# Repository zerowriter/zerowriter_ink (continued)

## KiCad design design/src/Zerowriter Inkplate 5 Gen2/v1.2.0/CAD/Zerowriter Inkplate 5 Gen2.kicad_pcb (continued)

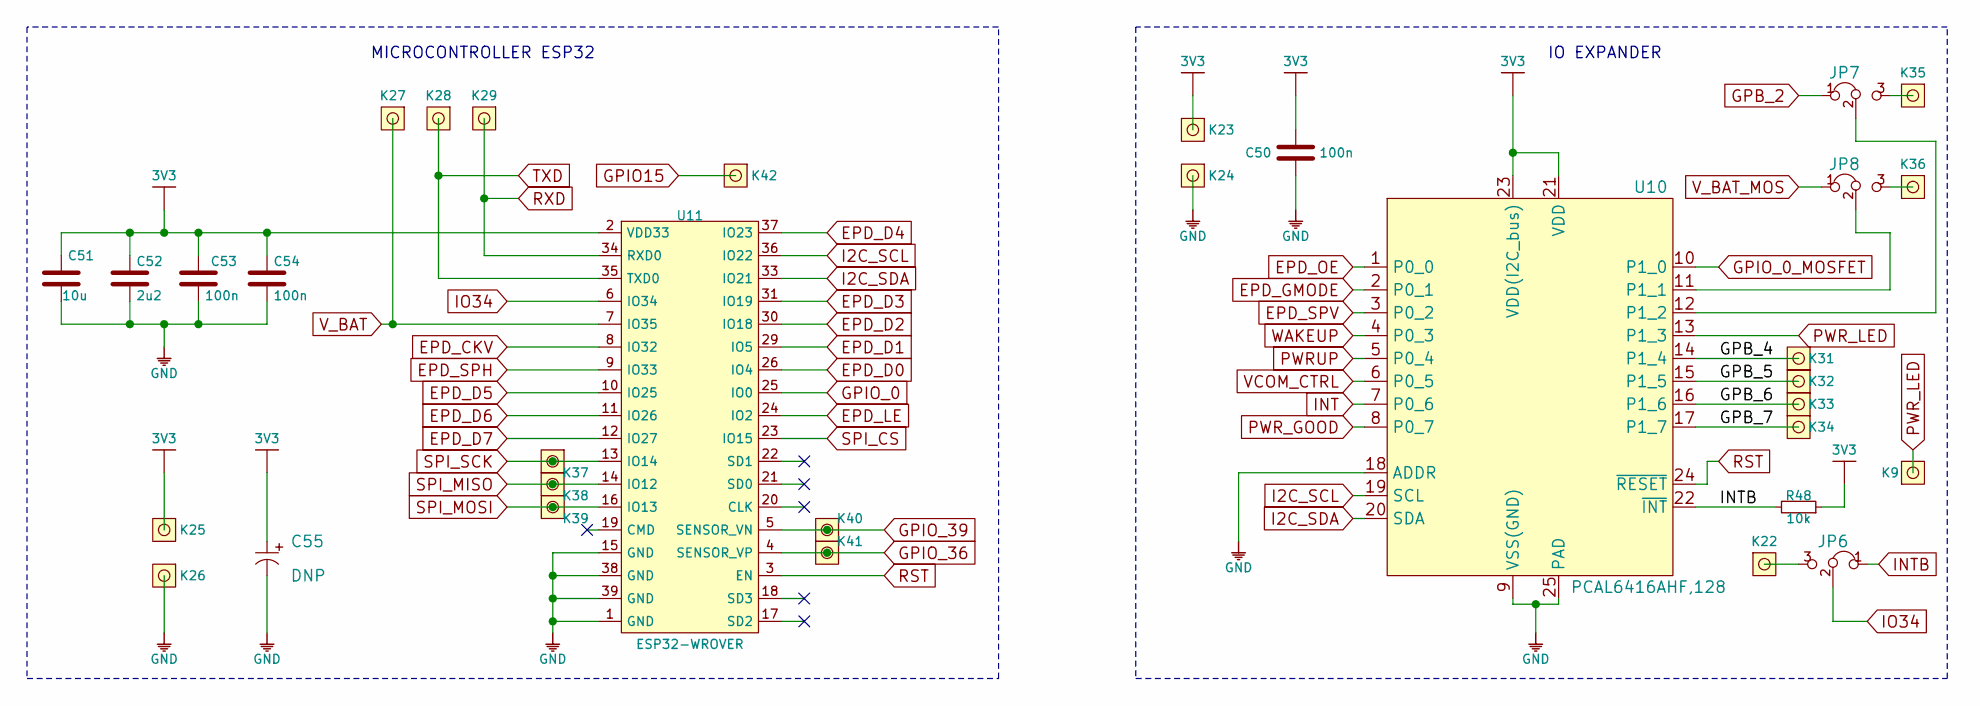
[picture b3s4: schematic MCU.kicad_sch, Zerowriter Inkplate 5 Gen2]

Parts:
C50, C53, C54: 100n; 0603C
C51: 10u; 1206C
C52: 2u2; 0603C
C55: DNP; 2917C
JP6, JP7, JP8: SMD_JUMPER_3_PAD_CONNECTED_LEFT_TRACE
K9, K22, K23, K24, K25, K26, K27, K28, K29, K31, K32, K33, K34, K35, K36, K37, K38, K39, K40, K41, K42: HEADER_MALE_1X1_Inkplate
R48: 10k; 0603R
U10: PCAL6416AHF,128
U11: ESP32-WROVER

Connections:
3V3: C50.2, C51.2, C52.2, C53.2, C54.2, C55.1 (+), K23.1, K25.1, R48.1, U10.21 (VDD), U10.23 (VDD(I2C_bus)), U11.2 (VDD33); also elsewhere on the board
/MCU/GPB_4: K31.1, U10.14 (P1_4)
/MCU/GPB_5: K32.1, U10.15 (P1_5)
/MCU/GPB_6: K33.1, U10.16 (P1_6)
/MCU/GPB_7: K34.1, U10.17 (P1_7)
EPD_CKV: U11.8 (IO32); also elsewhere on the board
EPD_D0: U11.26 (IO4); also elsewhere on the board
EPD_D1: U11.29 (IO5); also elsewhere on the board
EPD_D2: U11.30 (IO18); also elsewhere on the board
EPD_D3: U11.31 (IO19); also elsewhere on the board
EPD_D4: U11.37 (IO23); also elsewhere on the board
EPD_D5: U11.10 (IO25); also elsewhere on the board
EPD_D6: U11.11 (IO26); also elsewhere on the board
EPD_D7: U11.12 (IO27); also elsewhere on the board
EPD_GMODE: U10.2 (P0_1); also elsewhere on the board
EPD_LE: U11.24 (IO2); also elsewhere on the board
EPD_OE: U10.1 (P0_0); also elsewhere on the board
EPD_SPH: U11.9 (IO33); also elsewhere on the board
EPD_SPV: U10.3 (P0_2); also elsewhere on the board
GND: C50.1, C51.1, C52.1, C53.1, C54.1, C55.2 (-), K24.1, K26.1, U10.9 (VSS(GND)), U10.18 (ADDR), U10.25 (PAD), U11.1 (GND), U11.15 (GND), U11.38 (GND), U11.39 (GND); also elsewhere on the board
GPB_2: JP7.1; also elsewhere on the board
GPIO15: K42.1; also elsewhere on the board
GPIO_0: U11.25 (IO0); also elsewhere on the board
GPIO_0_MOSFET: U10.10 (P1_0); also elsewhere on the board
GPIO_36: K41.1, U11.4 (SENSOR_VP); also elsewhere on the board
GPIO_39: K40.1, U11.5 (SENSOR_VN); also elsewhere on the board
I2C_SCL: U10.19 (SCL), U11.36 (IO22); also elsewhere on the board
I2C_SDA: U10.20 (SDA), U11.33 (IO21); also elsewhere on the board
INT: U10.7 (P0_6); also elsewhere on the board
INTB: JP6.1, R48.2, U10.22 (~INT); also elsewhere on the board
IO34: JP6.2, U11.6 (IO34); also elsewhere on the board
unnamed: JP6.3, K22.1
unnamed: JP7.3, K35.1
unnamed: JP8.3, K36.1
unnamed: JP8.2, U10.11 (P1_1)
unnamed: JP7.2, U10.12 (P1_2)
PWRUP: U10.5 (P0_4); also elsewhere on the board
PWR_GOOD: U10.8 (P0_7); also elsewhere on the board
PWR_LED: K9.1, U10.13 (P1_3); also elsewhere on the board
RST: U10.24 (~RESET), U11.3 (EN); also elsewhere on the board
RXD: K29.1, U11.34 (RXD0); also elsewhere on the board
SPI_CS: U11.23 (IO15); also elsewhere on the board
SPI_MISO: K38.1, U11.14 (IO12); also elsewhere on the board
SPI_MOSI: K39.1, U11.16 (IO13); also elsewhere on the board
SPI_SCK: K37.1, U11.13 (IO14); also elsewhere on the board
TXD: K28.1, U11.35 (TXD0); also elsewhere on the board
VCOM_CTRL: U10.6 (P0_5); also elsewhere on the board
V_BAT: K27.1, U11.7 (IO35); also elsewhere on the board
V_BAT_MOS: JP8.1; also elsewhere on the board
WAKEUP: U10.4 (P0_3); also elsewhere on the board

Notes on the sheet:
IO EXPANDER
MICROCONTROLLER ESP32

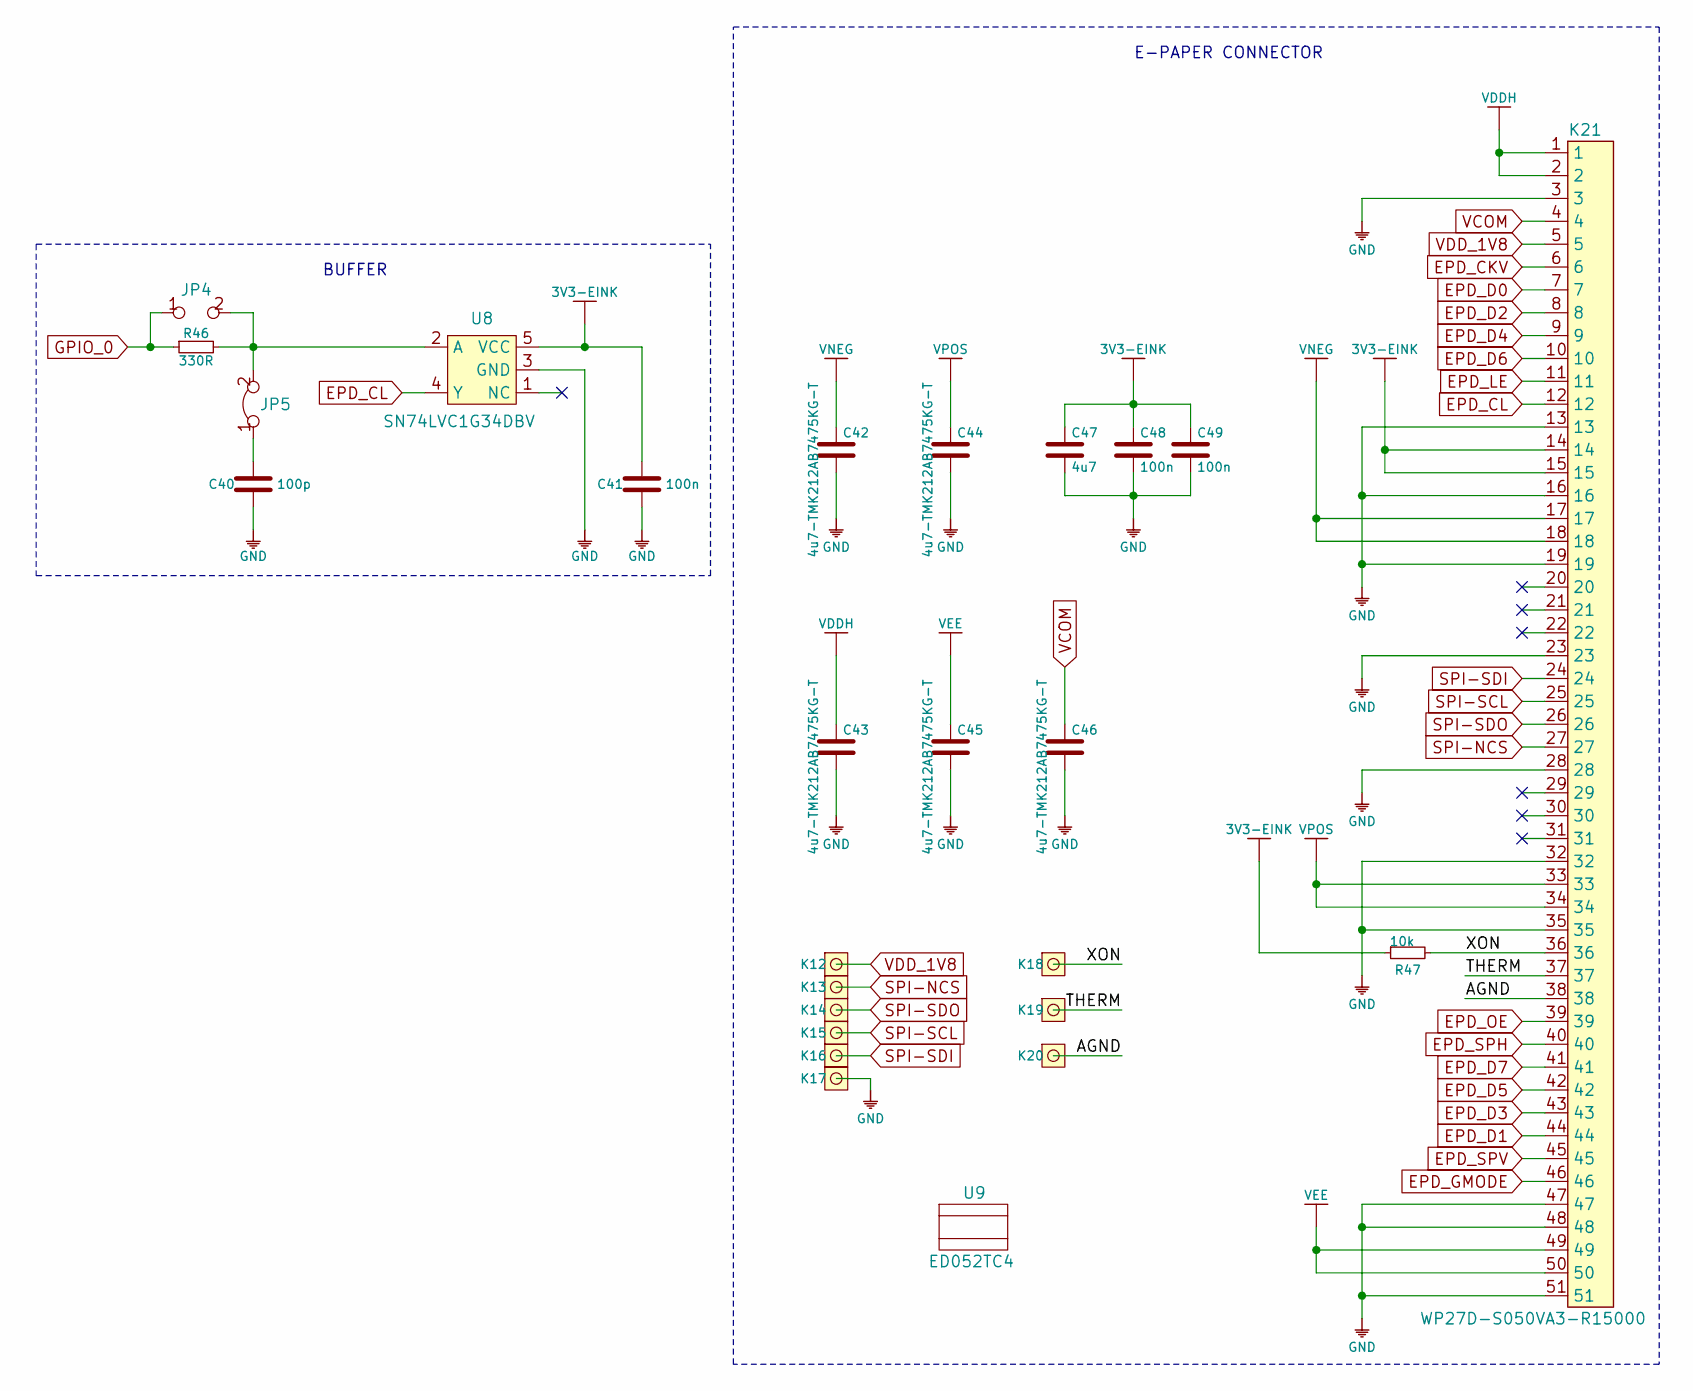
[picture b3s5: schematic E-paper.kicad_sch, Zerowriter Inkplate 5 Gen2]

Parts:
C40: 100p; 0603C
C41, C48, C49: 100n; 0603C
C42, C43, C44, C45, C46: 4u7-TMK212AB7475KG-T; 0805C
C47: 4u7; 0603C
JP4: SMD_JUMPER
JP5: SMD-JUMPER-CONNECTED_TRACE_SOLDERMASK
K12, K13, K14, K15, K16, K17, K18, K19, K20: HEADER_MALE_1X1_Inkplate
K21: WP27D-S050VA3-R15000
R46: 330R; 0603R
R47: 10k; 0603R
U8: SN74LVC1G34DBV
U9: ED052TC4

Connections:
3V3-EINK: C41.2, C47.2, C48.2, C49.2, K21.14, K21.15, R47.1, U8.5 (VCC); also elsewhere on the board
/E-paper/AGND: K20.1, K21.38
/E-paper/THERM: K19.1, K21.37
/E-paper/XON: K18.1, K21.36, R47.2
EPD_CKV: K21.6; also elsewhere on the board
EPD_CL: K21.12, U8.4 (Y)
EPD_D0: K21.7; also elsewhere on the board
EPD_D1: K21.44; also elsewhere on the board
EPD_D2: K21.8; also elsewhere on the board
EPD_D3: K21.43; also elsewhere on the board
EPD_D4: K21.9; also elsewhere on the board
EPD_D5: K21.42; also elsewhere on the board
EPD_D6: K21.10; also elsewhere on the board
EPD_D7: K21.41; also elsewhere on the board
EPD_GMODE: K21.46; also elsewhere on the board
EPD_LE: K21.11; also elsewhere on the board
EPD_OE: K21.39; also elsewhere on the board
EPD_SPH: K21.40; also elsewhere on the board
EPD_SPV: K21.45; also elsewhere on the board
GND: C40.1, C41.1, C42.1, C43.1, C44.1, C45.1, C46.1, C47.1, C48.1, C49.1, K17.1, K21.3, K21.13, K21.16, K21.19, K21.23, K21.28, K21.32, K21.35, K21.47, K21.48, K21.51, U8.3 (GND); also elsewhere on the board
GPIO_0: JP4.1, R46.1; also elsewhere on the board
unnamed: C40.2, JP5.1
unnamed: JP4.2, JP5.2, R46.2, U8.2 (A)
SPI-NCS: K13.1, K21.27
SPI-SCL: K15.1, K21.25
SPI-SDI: K16.1, K21.24
SPI-SDO: K14.1, K21.26
VCOM: C46.2, K21.4; also elsewhere on the board
VDDH: C43.2, K21.1, K21.2; also elsewhere on the board
VDD_1V8: K12.1, K21.5
VEE: C45.2, K21.49, K21.50; also elsewhere on the board
VNEG: C42.2, K21.17, K21.18; also elsewhere on the board
VPOS: C44.2, K21.33, K21.34; also elsewhere on the board

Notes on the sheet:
E-PAPER CONNECTOR
BUFFER

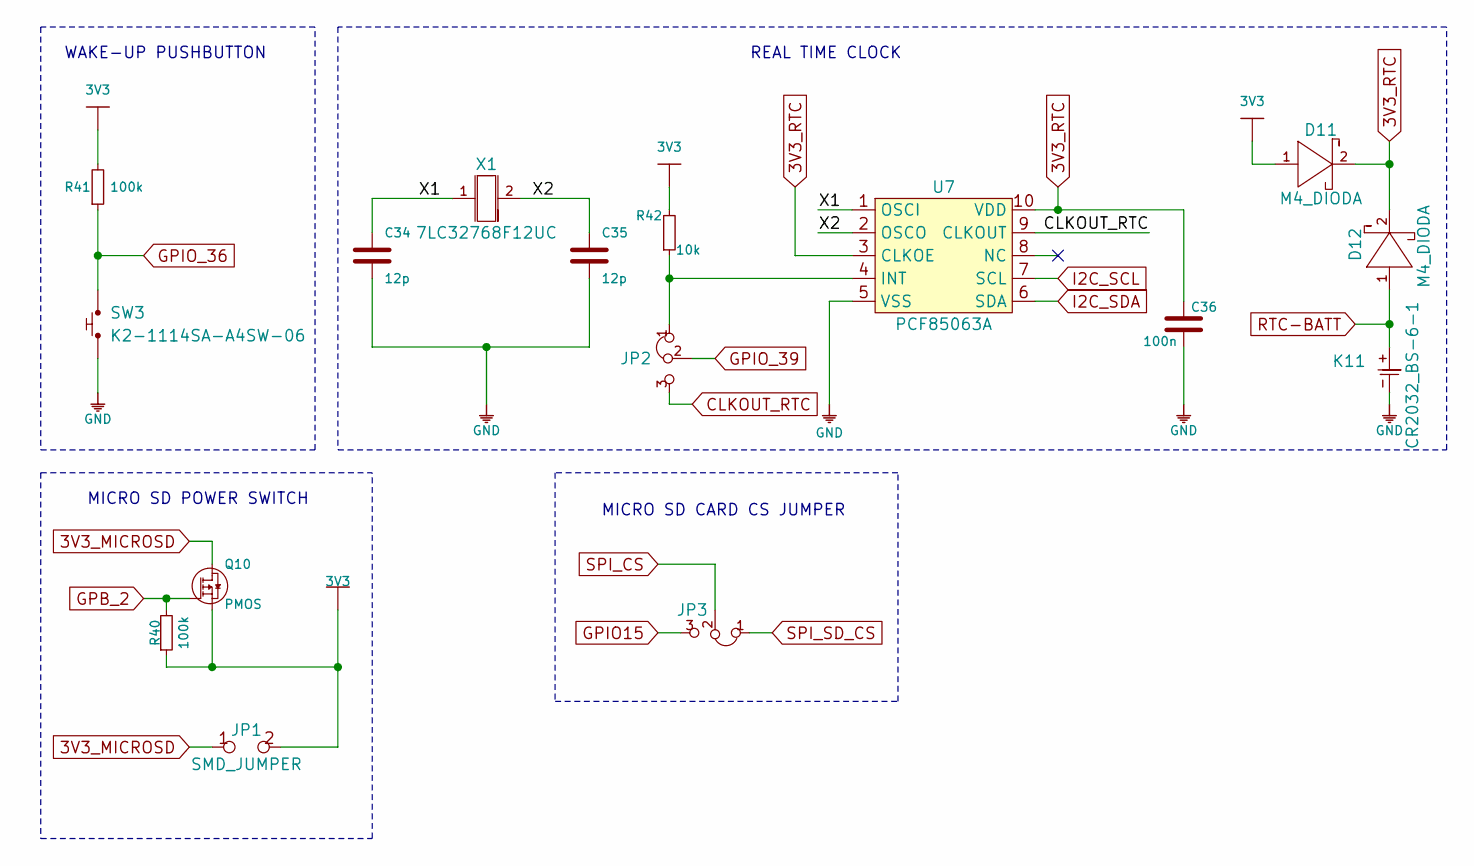
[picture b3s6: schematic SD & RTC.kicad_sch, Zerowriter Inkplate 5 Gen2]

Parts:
C34, C35: 12p; 0603C
C36: 100n; 0603C
D11, D12: M4_DIODA
JP1: SMD_JUMPER
JP2, JP3: SMD_JUMPER_3_PAD_CONNECTED_LEFT_TRACE
K11: CR2032_BS-6-1; CR2032-BS-6-1
Q10: PMOS; SOT-23-3
R40, R41: 100k; 0603R
R42: 10k; 0603R
SW3: K2-1114SA-A4SW-06
U7: PCF85063A
X1: 7LC32768F12UC; ABS07AIG-32.768KHZ-7-D-T

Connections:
3V3: D11.1 (A), JP1.2, Q10.2 (S), R40.1, R41.2, R42.2; also elsewhere on the board
3V3_MICROSD: JP1.1, Q10.3 (D); also elsewhere on the board
3V3_RTC: C36.2, D11.2 (K), D12.2 (K), U7.3 (CLKOE), U7.10 (VDD); also elsewhere on the board
/SD & RTC/X1: C34.2, U7.1 (OSCI), X1.1
/SD & RTC/X2: C35.2, U7.2 (OSCO), X1.2
CLKOUT_RTC: JP2.3, U7.9 (CLKOUT); also elsewhere on the board
GND: C34.1, C35.1, C36.1, K11.-, SW3.1, U7.5 (VSS); also elsewhere on the board
GPB_2: Q10.1 (G), R40.2; also elsewhere on the board
GPIO15: JP3.3; also elsewhere on the board
GPIO_36: R41.1, SW3.2; also elsewhere on the board
GPIO_39: JP2.2; also elsewhere on the board
I2C_SCL: U7.7 (SCL); also elsewhere on the board
I2C_SDA: U7.6 (SDA); also elsewhere on the board
unnamed: JP2.1, R42.1, U7.4 (INT)
RTC-BATT: D12.1 (A), K11.+; also elsewhere on the board
SPI_CS: JP3.2; also elsewhere on the board
SPI_SD_CS: JP3.1; also elsewhere on the board

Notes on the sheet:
REAL TIME CLOCK
MICRO SD CARD CS JUMPER
WAKE-UP PUSHBUTTON
MICRO SD POWER SWITCH

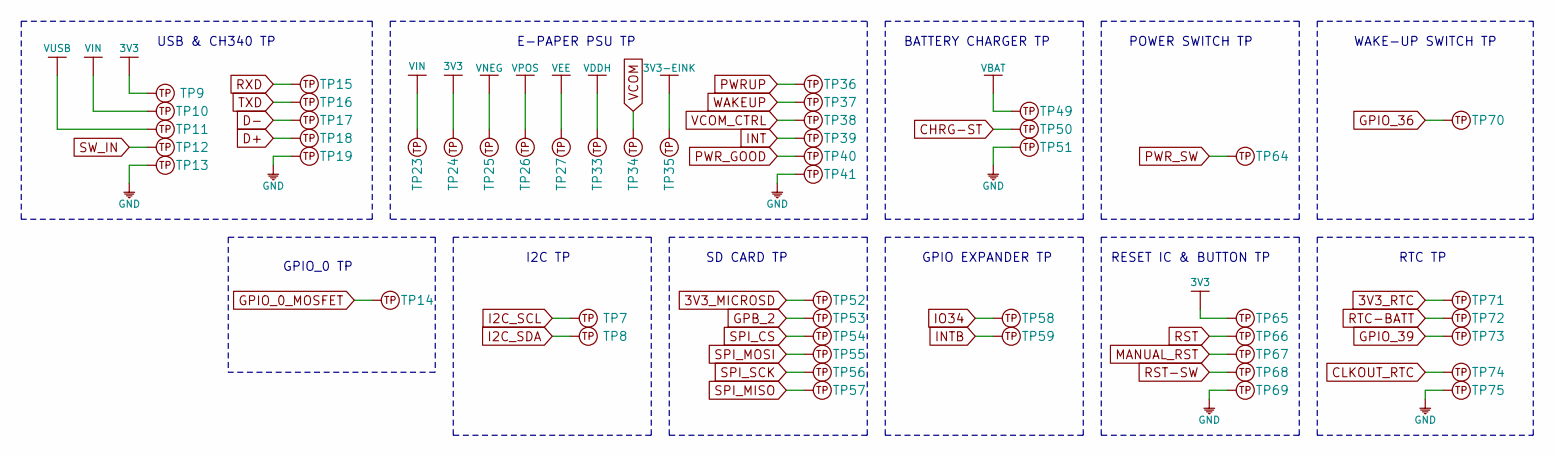
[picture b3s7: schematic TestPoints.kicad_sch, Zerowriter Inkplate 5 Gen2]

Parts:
TP7, TP8, TP9, TP10, TP11, TP12, TP13, TP14, TP15, TP16, TP17, TP18, TP19, TP23, TP24, TP25, TP26, TP27, TP33, TP34, TP35, TP36, TP37, TP38, TP39, TP40, TP41, TP49, TP50, TP51, TP52, TP53, TP54, TP55, TP56, TP57, TP58, TP59, TP64, TP65, TP66, TP67, TP68, TP69, TP70, TP71, TP72, TP73, TP74, TP75: Test_Point_SMD_0.8mm

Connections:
3V3: TP9.TP, TP24.TP, TP65.TP; also elsewhere on the board
3V3-EINK: TP35.TP; also elsewhere on the board
3V3_MICROSD: TP52.TP; also elsewhere on the board
3V3_RTC: TP71.TP; also elsewhere on the board
CHRG-ST: TP50.TP; also elsewhere on the board
CLKOUT_RTC: TP74.TP; also elsewhere on the board
D+: TP18.TP; also elsewhere on the board
D-: TP17.TP; also elsewhere on the board
GND: TP13.TP, TP19.TP, TP41.TP, TP51.TP, TP69.TP, TP75.TP; also elsewhere on the board
GPB_2: TP53.TP; also elsewhere on the board
GPIO_0_MOSFET: TP14.TP; also elsewhere on the board
GPIO_36: TP70.TP; also elsewhere on the board
GPIO_39: TP73.TP; also elsewhere on the board
I2C_SCL: TP7.TP; also elsewhere on the board
I2C_SDA: TP8.TP; also elsewhere on the board
INT: TP39.TP; also elsewhere on the board
INTB: TP59.TP; also elsewhere on the board
IO34: TP58.TP; also elsewhere on the board
MANUAL_RST: TP67.TP; also elsewhere on the board
PWRUP: TP36.TP; also elsewhere on the board
PWR_GOOD: TP40.TP; also elsewhere on the board
PWR_SW: TP64.TP; also elsewhere on the board
RST: TP66.TP; also elsewhere on the board
RST-SW: TP68.TP; also elsewhere on the board
RTC-BATT: TP72.TP; also elsewhere on the board
RXD: TP15.TP; also elsewhere on the board
SPI_CS: TP54.TP; also elsewhere on the board
SPI_MISO: TP57.TP; also elsewhere on the board
SPI_MOSI: TP55.TP; also elsewhere on the board
SPI_SCK: TP56.TP; also elsewhere on the board
SW_IN: TP12.TP; also elsewhere on the board
TXD: TP16.TP; also elsewhere on the board
VBAT: TP49.TP; also elsewhere on the board
VCOM: TP34.TP; also elsewhere on the board
VCOM_CTRL: TP38.TP; also elsewhere on the board
VDDH: TP33.TP; also elsewhere on the board
VEE: TP27.TP; also elsewhere on the board
VIN: TP10.TP, TP23.TP; also elsewhere on the board
VNEG: TP25.TP; also elsewhere on the board
VPOS: TP26.TP; also elsewhere on the board
VUSB: TP11.TP; also elsewhere on the board
WAKEUP: TP37.TP; also elsewhere on the board

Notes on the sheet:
GPIO EXPANDER TP
POWER SWITCH TP
RESET IC & BUTTON TP
BATTERY CHARGER TP
GPIO_0 TP
SD CARD TP
I2C TP
USB & CH340 TP
WAKE-UP SWITCH TP
RTC TP
E-PAPER PSU TP

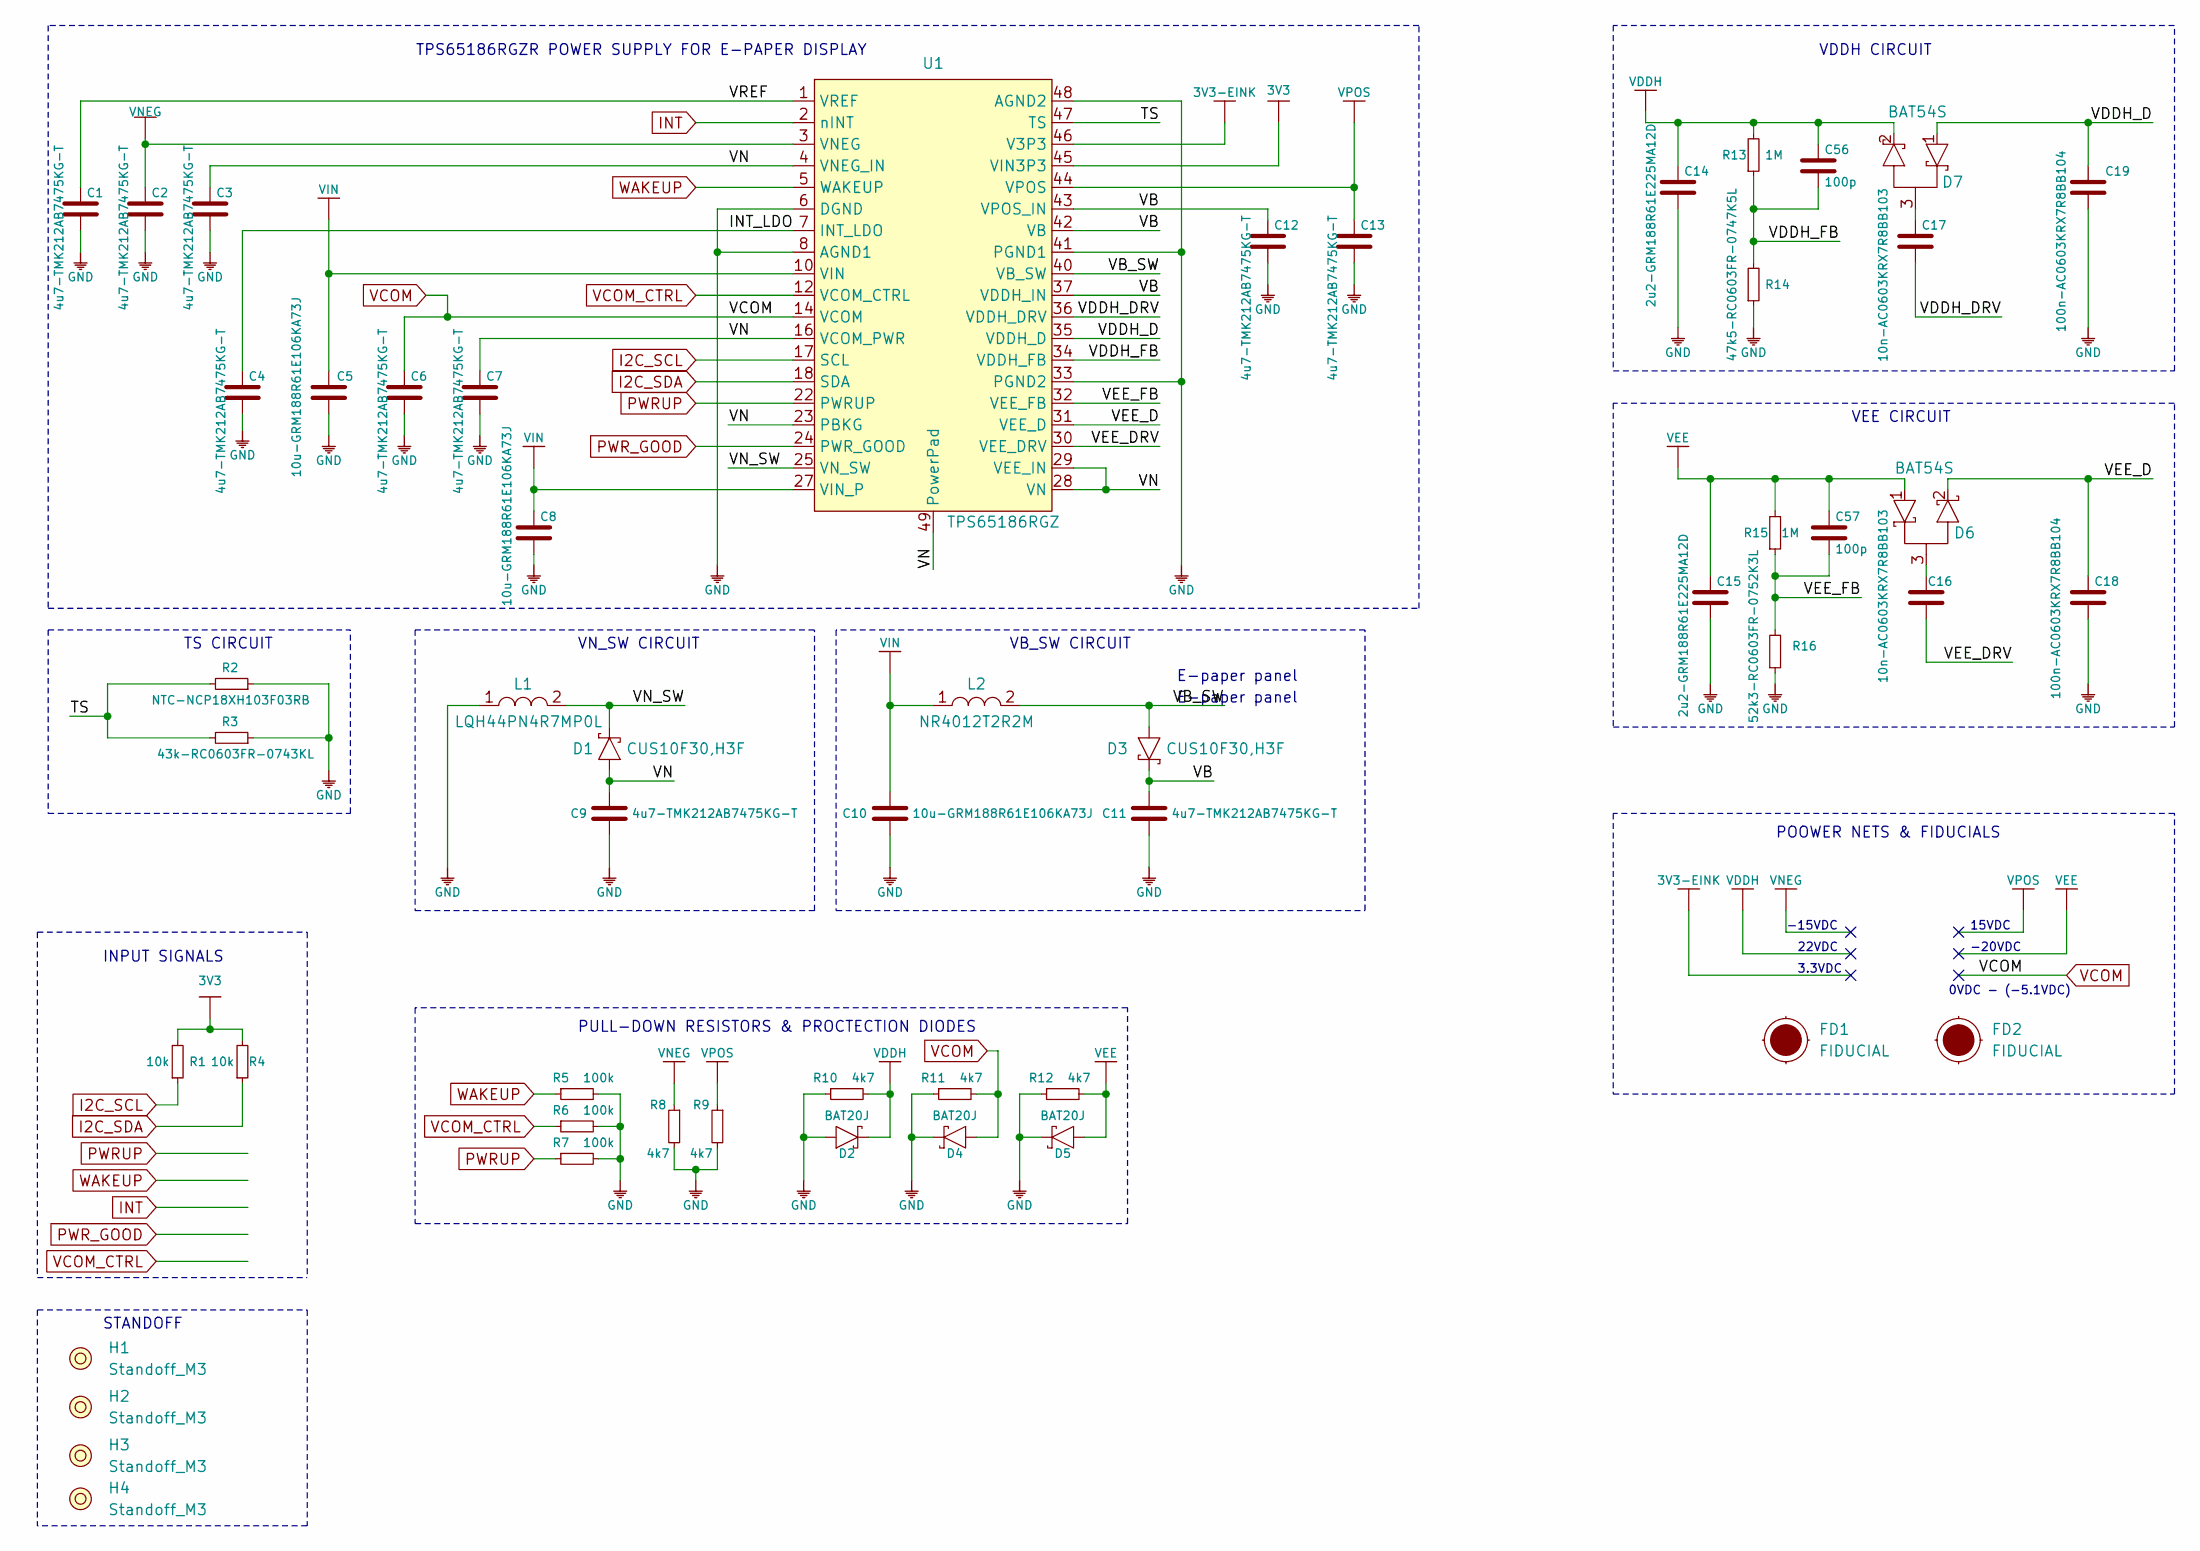
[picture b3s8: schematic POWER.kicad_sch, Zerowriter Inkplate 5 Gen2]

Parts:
C1, C2, C3, C4, C6, C7, C9, C11, C12, C13: 4u7-TMK212AB7475KG-T; 0805C
C5, C8, C10: 10u-GRM188R61E106KA73J; 0603C
C14, C15: 2u2-GRM188R61E225MA12D; 0603C
C16, C17: 10n-AC0603KRX7R8BB103; 0603C
C18, C19: 100n-AC0603KRX7R8BB104; 0603C
C56, C57: 100p; 0603C
D1, D3: CUS10F30,H3F; SOD-323-2
D2, D4, D5: BAT20J; SOD-323
D6, D7: BAT54S; SOT-23-3
FD1, FD2: FIDUCIAL
H1, H2, H3, H4: Standoff_M3
L1: LQH44PN4R7MP0L; 1515L
L2: NR4012T2R2M; NR4012
R1, R4: 10k; 0603R
R2: NTC-NCP18XH103F03RB; 0603R
R3: 43k-RC0603FR-0743KL; 0603R
R5, R6, R7: 100k; 0603R
R8, R9, R10, R11, R12: 4k7; 0603R
R13, R15: 1M; 0603R
R14: 47k5-RC0603FR-0747K5L; 0603R
R16: 52k3-RC0603FR-0752K3L; 0603R
U1: TPS65186RGZ; VQFN-49

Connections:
3V3: R1.2, R4.2, U1.45 (VIN3P3); also elsewhere on the board
3V3-EINK: U1.46 (V3P3); also elsewhere on the board
/POWER/INT_LDO: C4.2, U1.7 (INT_LDO)
/POWER/TS: R2.2, R3.2, U1.47 (TS)
/POWER/VB: C11.1, C12.2, D3.1 (C), U1.37 (VDDH_IN), U1.42 (VB), U1.43 (VPOS_IN)
/POWER/VB_SW: D3.2 (A), L2.2, U1.40 (VB_SW)
/POWER/VDDH_D: C19.2, D7.1 (A), U1.35 (VDDH_D)
/POWER/VDDH_DRV: C17.1, U1.36 (VDDH_DRV)
/POWER/VDDH_FB: C56.1, R13.1, R14.2, U1.34 (VDDH_FB)
/POWER/VEE_D: C18.2, D6.2 (K), U1.31 (VEE_D)
/POWER/VEE_DRV: C16.2, U1.30 (VEE_DRV)
/POWER/VEE_FB: C57.1, R15.1, R16.2, U1.32 (VEE_FB)
/POWER/VN: C3.2, C7.2, C9.1, D1.2 (A), U1.4 (VNEG_IN), U1.16 (VCOM_PWR), U1.23 (PBKG), U1.28 (VN), U1.29 (VEE_IN), U1.49 (PowerPad)
/POWER/VN_SW: D1.1 (C), L1.2, U1.25 (VN_SW)
/POWER/VREF: C1.2, U1.1 (VREF)
GND: C1.1, C2.1, C3.1, C4.1, C5.1, C6.1, C7.1, C8.1, C9.2, C10.1, C11.2, C12.1, C13.1, C14.1, C15.1, C18.1, C19.1, D2.1 (A), D4.2 (C), D5.2 (C), L1.1, R2.1, R3.1, R5.2, R6.2, R7.2, R8.2, R9.2, R10.1, R11.1, R12.1, R14.1, R16.1, U1.6 (DGND), U1.8 (AGND1), U1.33 (PGND2), U1.41 (PGND1), U1.48 (AGND2); also elsewhere on the board
I2C_SCL: R1.1, U1.17 (SCL); also elsewhere on the board
I2C_SDA: R4.1, U1.18 (SDA); also elsewhere on the board
INT: U1.2 (nINT); also elsewhere on the board
unnamed: C16.1, D6.3
unnamed: C17.2, D7.3
PWRUP: R7.1, U1.22 (PWRUP); also elsewhere on the board
PWR_GOOD: U1.24 (PWR_GOOD); also elsewhere on the board
VCOM: C6.2, D4.1 (A), R11.2, U1.14 (VCOM); also elsewhere on the board
VCOM_CTRL: R6.1, U1.12 (VCOM_CTRL); also elsewhere on the board
VDDH: C14.2, C56.2, D2.2 (C), D7.2 (K), R10.2, R13.2; also elsewhere on the board
VEE: C15.2, C57.2, D5.1 (A), D6.1 (A), R12.2, R15.2; also elsewhere on the board
VIN: C5.2, C8.2, C10.2, L2.1, U1.10 (VIN), U1.27 (VIN_P); also elsewhere on the board
VNEG: C2.2, R8.1, U1.3 (VNEG); also elsewhere on the board
VPOS: C13.2, R9.1, U1.44 (VPOS); also elsewhere on the board
WAKEUP: R5.1, U1.5 (WAKEUP); also elsewhere on the board

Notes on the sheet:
TS CIRCUIT
VDDH CIRCUIT
POOWER NETS & FIDUCIALS
INPUT SIGNALS
E-paper panel
-15VDC
VEE CIRCUIT
TPS65186RGZR POWER SUPPLY FOR E-PAPER DISPLAY
VN_SW CIRCUIT
0VDC - (-5.1VDC)
15VDC
22VDC
PULL-DOWN RESISTORS & PROCTECTION DIODES
VB_SW CIRCUIT
STANDOFF
3.3VDC
-20VDC

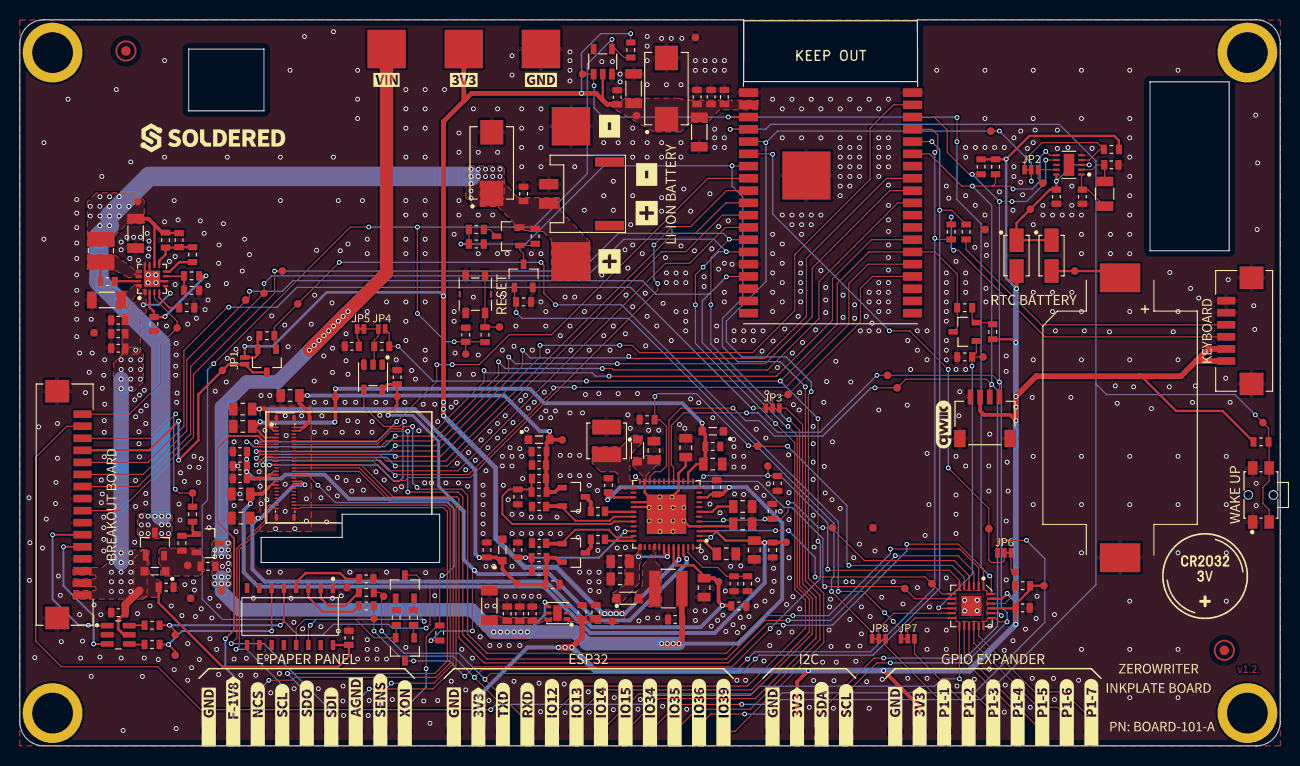
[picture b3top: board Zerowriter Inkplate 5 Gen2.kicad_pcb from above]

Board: 2 copper layers, 130.6 x 75.2 mm, 316 parts (0 on the bottom side), 125 nets.

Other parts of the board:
kibuzzard-63F89A5B: G***; kibuzzard-63F89A5B
kibuzzard-63F89A6D: G***; kibuzzard-63F89A6D
kibuzzard-63F89A8C: G***; kibuzzard-63F89A8C
kibuzzard-63F89A49: G***; kibuzzard-63F89A49
kibuzzard-63F89AA1: G***; kibuzzard-63F89AA1
kibuzzard-63F89AAD: G***; kibuzzard-63F89AAD
kibuzzard-63F89AB9: G***; kibuzzard-63F89AB9
kibuzzard-63F89AC1: G***; kibuzzard-63F89AC1
kibuzzard-63F89ACB: G***; kibuzzard-63F89ACB
kibuzzard-63F89AD4: G***; kibuzzard-63F89AD4
kibuzzard-63F89AEB: G***; kibuzzard-63F89AEB
kibuzzard-63F89B1A: G***; kibuzzard-63F89B1A
kibuzzard-63F89B2E: G***; kibuzzard-63F89B2E
kibuzzard-63F89B70: G***; kibuzzard-63F89B70
kibuzzard-63F89B77: G***; kibuzzard-63F89B77
kibuzzard-63F89B85: G***; kibuzzard-63F89B85
kibuzzard-63F89F9C: G***; kibuzzard-63F89F9C
kibuzzard-63F89F95: G***; kibuzzard-63F89F95
kibuzzard-63F89FA3: G***; kibuzzard-63F89FA3
kibuzzard-63F89FAA: G***; kibuzzard-63F89FAA
kibuzzard-63F897A7: G***; kibuzzard-63F897A7
kibuzzard-63F897B8: G***; kibuzzard-63F897B8
kibuzzard-63F897D2: G***; kibuzzard-63F897D2
kibuzzard-63F897E2: G***; kibuzzard-63F897E2
kibuzzard-63F897FB: G***; kibuzzard-63F897FB
kibuzzard-63F898AB: G***; kibuzzard-63F898AB
kibuzzard-63F898C1: G***; kibuzzard-63F898C1
kibuzzard-63F898D0: G***; kibuzzard-63F898D0
kibuzzard-63F898D8: G***; kibuzzard-63F898D8
kibuzzard-63F898F1: G***; kibuzzard-63F898F1
kibuzzard-63F898FB: G***; kibuzzard-63F898FB
kibuzzard-63F899CC: G***; kibuzzard-63F899CC
kibuzzard-63F899DF: G***; kibuzzard-63F899DF
kibuzzard-63F8973B, kibuzzard-63F8973B#2: G***; kibuzzard-63F8973B
kibuzzard-63F8983A: G***; kibuzzard-63F8983A
kibuzzard-63F8984A: G***; kibuzzard-63F8984A
kibuzzard-63F89764: G***; kibuzzard-63F89764
kibuzzard-63F89780: G***; kibuzzard-63F89780
kibuzzard-63F89796: G***; kibuzzard-63F89796
kibuzzard-63F89823: G***; kibuzzard-63F89823
kibuzzard-63F89858: G***; kibuzzard-63F89858
kibuzzard-63F89870: G***; kibuzzard-63F89870
kibuzzard-63F89882: G***; kibuzzard-63F89882
kibuzzard-63F89892: G***; kibuzzard-63F89892
kibuzzard-63F89913: G***; kibuzzard-63F89913
kibuzzard-63F89923: G***; kibuzzard-63F89923
kibuzzard-63F89937: G***; kibuzzard-63F89937
kibuzzard-63F89944: G***; kibuzzard-63F89944
kibuzzard-63F89953: G***; kibuzzard-63F89953
kibuzzard-63F89964: G***; kibuzzard-63F89964
kibuzzard-63F89979: G***; kibuzzard-63F89979
kibuzzard-63F89994: G***; kibuzzard-63F89994
kibuzzard-63FCACFE: G***; kibuzzard-63FCACFE
kibuzzard-63FCAF1B: G***; kibuzzard-63FCAF1B
kibuzzard-63FCAF23: G***; kibuzzard-63FCAF23
kibuzzard-67AA12B7: G***; kibuzzard-67AA12B7
kibuzzard-672A3648: G***; kibuzzard-672A3648
kibuzzard-68300E22: G***; kibuzzard-68300E22
kibuzzard-68300E82: G***; kibuzzard-68300E82
kibuzzard-68300E91: G***; kibuzzard-68300E91
kibuzzard-65360082: G***; kibuzzard-65360082

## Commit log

2026-01-27 added updater
2026-01-27 added compiled fonts
2026-01-27 fonts
2026-01-30 update
    bug fix - line spacing after newline chars (\n)
2026-02-12 firmware push
2026-02-13 Kicad Keyboard files
2026-05-13 source files
